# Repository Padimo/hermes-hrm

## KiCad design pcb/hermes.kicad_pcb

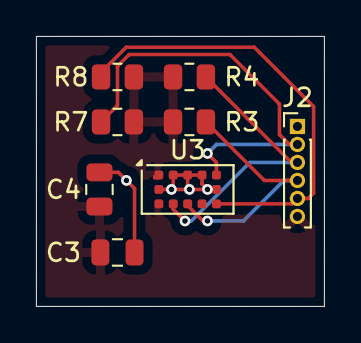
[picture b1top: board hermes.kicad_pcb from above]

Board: 2 copper layers, 16.0 x 15.0 mm, 8 parts (0 on the bottom side), 6 nets.

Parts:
C3: 100nF; C_0805_2012Metric
C4: 4.7uF; C_0805_2012Metric
J2: Conn_01x06_Pin; PinHeader_1x06_P1.00mm_Vertical
R3, R4, R7, R8: 5.1k; R_0805_2012Metric
U3: VL53L1CXV0FY1; ST_VL53L1x

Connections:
+3V3: C3.1, C4.1, J2.6, R3.1, R4.1, R7.1, R8.1, U3.1 (AVDDVCSEL), U3.11 (AVDD)
GND: C3.2, C4.2, J2.1, U3.2 (AVSSVCSEL), U3.3 (GND), U3.4 (GND), U3.6 (GND), U3.12 (GND)
SCL: J2.3, R4.2, U3.10 (SCL)
SDA: J2.4, R3.2, U3.9 (SDA)
TOF_INT: J2.5, R8.2, U3.7 (GPIO1)
XSHUT: J2.2, R7.2, U3.5 (XSHUT)

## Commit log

2025-10-28 Added I2C pullups in schematic
2025-11-08 Added resistor in PCB
2025-11-13 Convert to ToF devboard (use previous versions for full Hermes board
